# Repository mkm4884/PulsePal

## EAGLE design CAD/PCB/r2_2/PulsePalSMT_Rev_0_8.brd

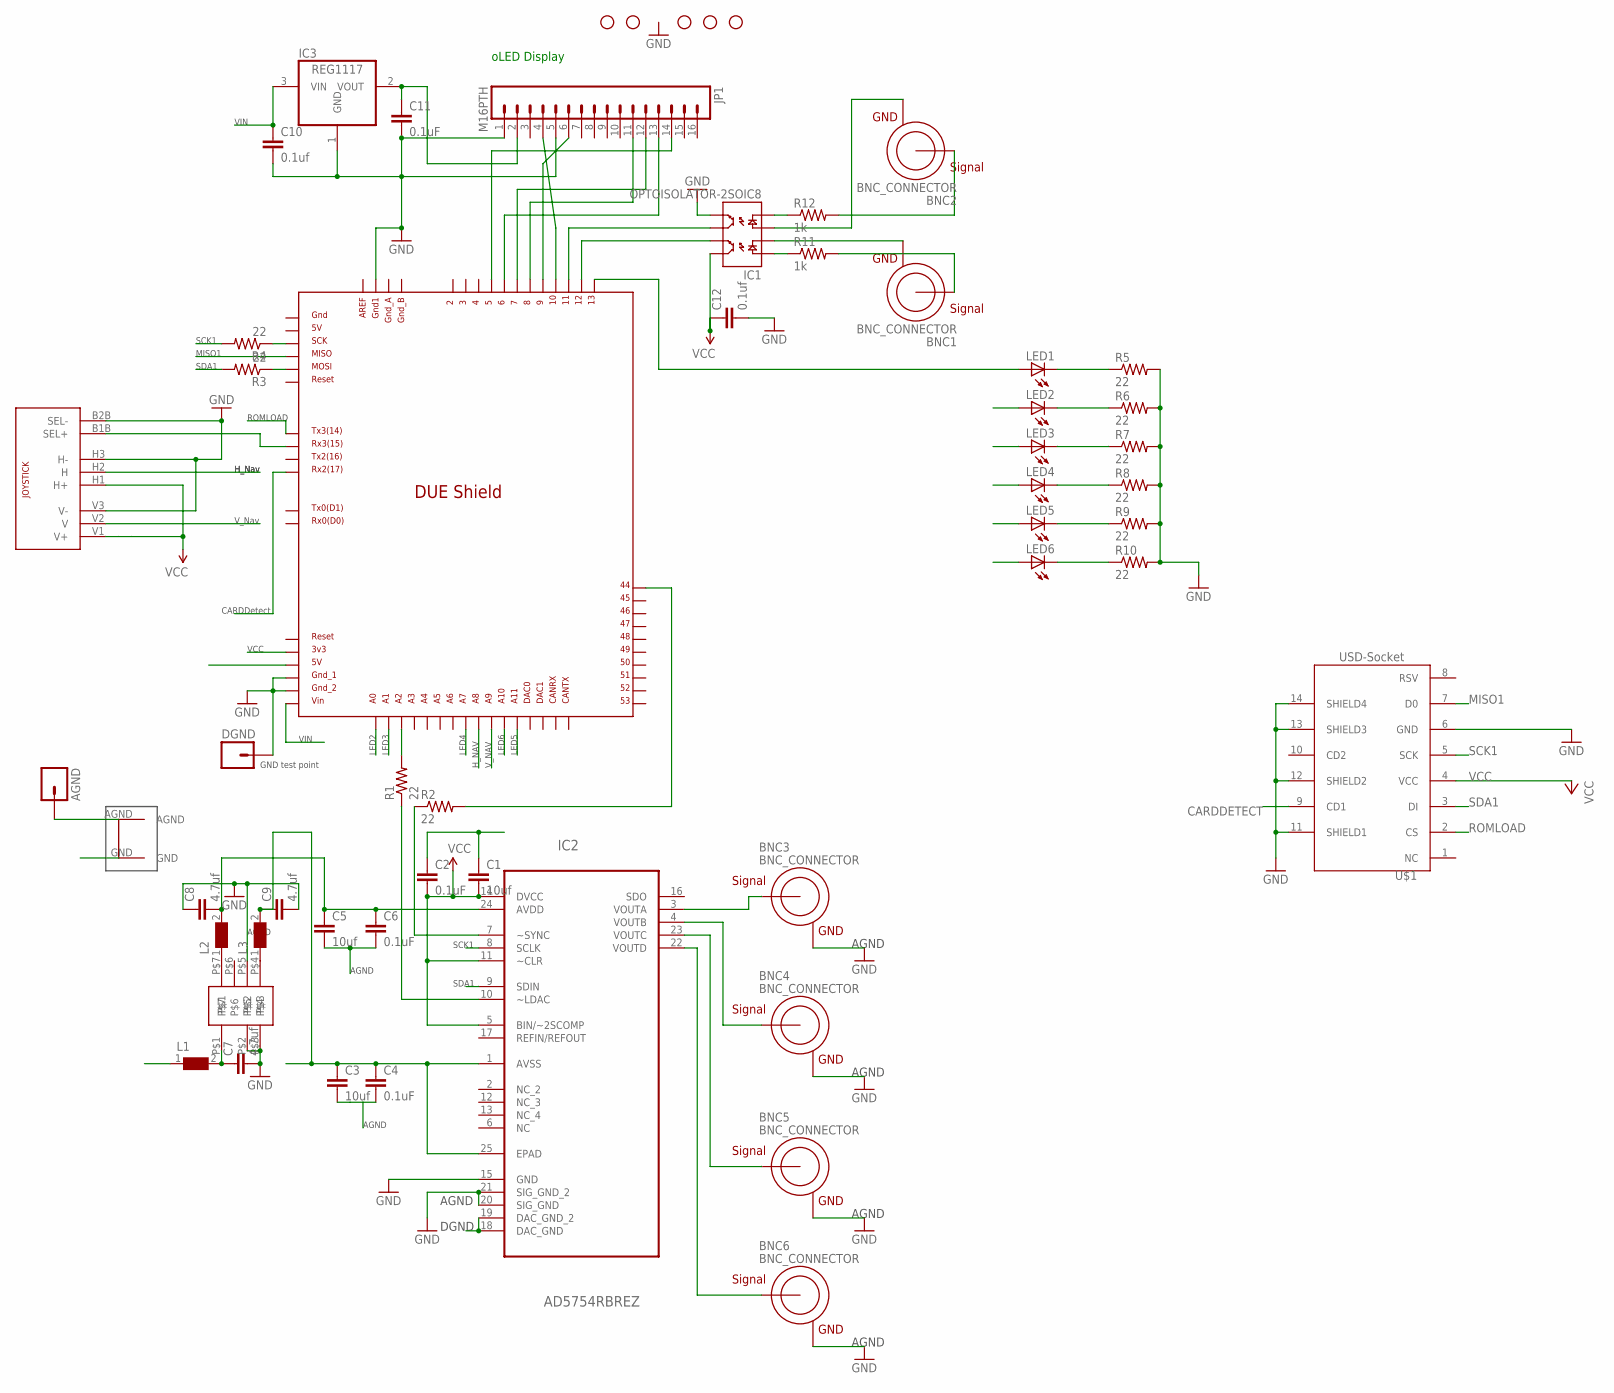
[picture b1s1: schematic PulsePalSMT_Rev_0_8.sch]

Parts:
AGND: M01PTH; 1X01
ARDUINO: DUE(NORMAL)
BNC1, BNC2, BNC3, BNC4, BNC5, BNC6: BNC_CONNECTOR
C1, C3, C5: 10uf; 1206@1
C2, C4, C6, C11: 0.1uF; 0805
C7, C8, C9: 4.7uf; 1206@1
C10: 0.1uf; 0805
C12: 0.1uf; 1206@1
DGND: M01PTH; 1X01
IC1: OPTOISOLATOR-2SOIC8; SO08-2
IC2: AD5754RBREZ; SOP65P640X120-25N
IC3: REG1117; SOT223
JP1: M16PTH; 1X16
JP2, JP5, JP6, JP8, JP9: STAND-OFF
JS1: RKJXV1124
L1, L2, L3: WE-CBF-742792118_1206; 1206
LED1, LED2, LED3, LED4, LED5, LED6: LEDCHIPLED_1206; CHIPLED_1206
R1, R2, R3, R4, R5, R6, R7, R8, R9, R10: 22; 1206
R11, R12: 1k; 1206
U2: TDK_LAMBDA_5_TO_BI_12_125MA
U3: 502570-0893
U$6: GNDPLANESHRT

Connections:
5V: ARDUINO.5V, C1.2, C2.2, IC2.5 (BIN/~2SCOMP), IC2.11 (~CLR), IC2.14 (DVCC), L1.1
AGND: AGND.1, BNC3.GND, BNC4.GND, BNC5.GND, BNC6.GND, C3.2, C4.2, C5.2, C6.2, IC2.15 (GND), IC2.18 (DAC_GND), IC2.19 (DAC_GND_2), IC2.20 (SIG_GND), IC2.21 (SIG_GND_2), U$6.AGND
CARDDETECT: ARDUINO.RX2, U3.9 (CD1)
GND: ARDUINO.GND1, ARDUINO.GND_1, ARDUINO.GND_2, C1.1, C2.1, C7.2, C8.1, C9.2, C10.2, C11.2, C12.2, DGND.1, IC1.5 (EM2), IC3.1 (GND), JP1.1, JP1.5, JS1.B2B (SEL-), JS1.H3 (H-), JS1.V3 (V-), R5.2, R6.2, R7.2, R8.2, R9.2, R10.2, U2.P$2, U2.P$3, U2.P$5, U3.6 (GND), U3.11 (SHIELD1), U3.12 (SHIELD2), U3.13 (SHIELD3), U3.14 (SHIELD4), U$6.GND
H_NAV: ARDUINO.A8, JS1.H2 (H)
LED2: ARDUINO.A0, LED2.A
LED3: ARDUINO.A1, LED3.A
LED4: ARDUINO.A7, LED4.A
LED5: ARDUINO.A11, LED5.A
LED6: ARDUINO.A10, LED6.A
MISO1: ARDUINO.MISO_ICSP, U3.7 (D0)
unnamed: L2.1, U2.P$7
unnamed: L3.1, U2.P$4
unnamed: BNC3.SIGNAL, IC2.3 (VOUTA)
unnamed: BNC4.SIGNAL, IC2.4 (VOUTB)
unnamed: BNC5.SIGNAL, IC2.23 (VOUTC)
unnamed: BNC6.SIGNAL, IC2.22 (VOUTD)
unnamed: BNC1.GND, IC1.2 (C1)
unnamed: BNC1.SIGNAL, R11.2
unnamed: BNC2.GND, IC1.3 (A2)
unnamed: BNC2.SIGNAL, R12.2
unnamed: ARDUINO.SCK_ICSP, R4.1
unnamed: ARDUINO.MOSI_ICSP, R3.1
unnamed: ARDUINO.44, R2.2
unnamed: ARDUINO.A2, R1.2
unnamed: IC2.7 (~SYNC), R2.1
unnamed: IC2.10 (~LDAC), R1.1
unnamed: ARDUINO.RX3, JS1.B1B (SEL+)
unnamed: ARDUINO.11, IC1.6 (CL2)
unnamed: C11.1, IC3.2 (VOUT), JP1.2
unnamed: LED1.C, R5.1
unnamed: LED2.C, R6.1
unnamed: LED3.C, R7.1
unnamed: LED4.C, R8.1
unnamed: LED5.C, R9.1
unnamed: LED6.C, R10.1
unnamed: IC1.1 (A1), R11.1
unnamed: IC1.4 (C2), R12.1
unnamed: ARDUINO.12, IC1.7 (EM1)
unnamed: ARDUINO.5, JP1.14
unnamed: ARDUINO.13, LED1.A
unnamed: ARDUINO.10, JP1.4
unnamed: ARDUINO.9, JP1.6
unnamed: ARDUINO.8, JP1.11
unnamed: ARDUINO.7, JP1.12
unnamed: ARDUINO.6, JP1.13
unnamed: C5.1, C6.1, C8.2, IC2.24 (AVDD), L2.2
unnamed: C3.1, C4.1, C9.1, IC2.1 (AVSS), IC2.25 (EPAD), L3.2
unnamed: C7.1, L1.2, U2.P$1
ROMLOAD: ARDUINO.TX3, U3.2 (CS)
SCK1: IC2.8 (SCLK), R4.2, U3.5 (SCK)
SDA1: IC2.9 (SDIN), R3.2, U3.3 (DI)
VCC: ARDUINO.3V3, C12.1, IC1.8 (CL1), JS1.H1 (H+), JS1.V1 (V+), U3.4 (VCC)
VIN: ARDUINO.VIN, C10.1, IC3.3 (VIN)
V_NAV: ARDUINO.A9, JS1.V2 (V)

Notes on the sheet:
oLED Display
AGND
SCK1
SDA1
DGND
VCC
ROMLOAD
LED2
LED3
LED4
LED5
LED6
GND test point
H_Nav
V_Nav
MISO1
H_NAV
V_NAV
VIN
CARDDetect

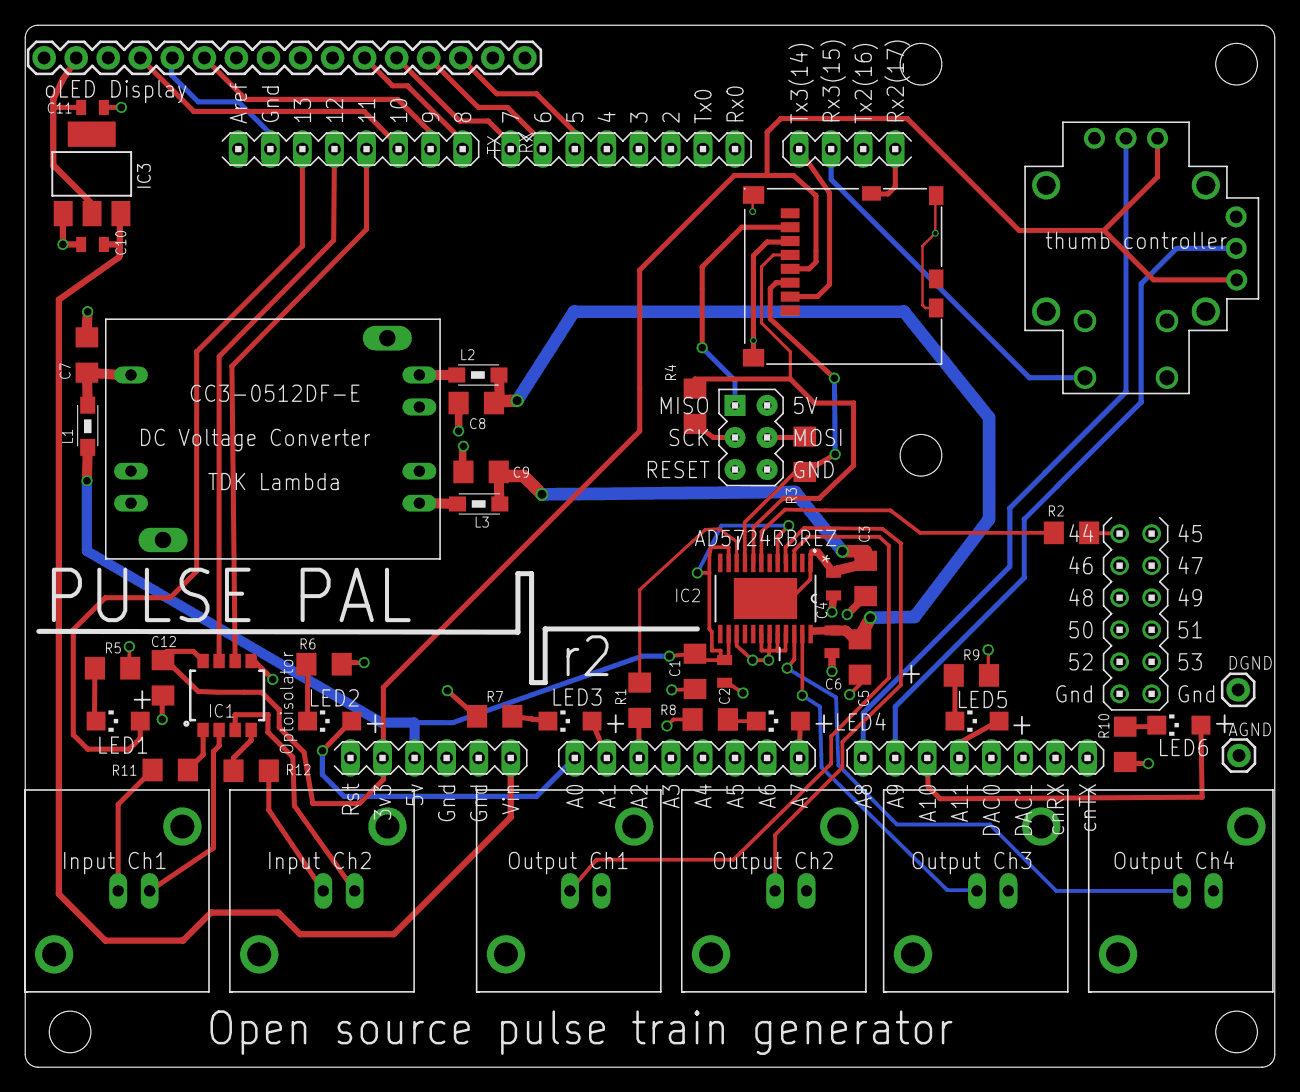
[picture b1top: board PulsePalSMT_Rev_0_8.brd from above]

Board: 4 copper layers, 99.0 x 82.6 mm, 55 parts (0 on the bottom side), 55 nets.

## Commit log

2019-08-09 Added r2.2 of the PCB to fit new SD card and thumbstick dimensions

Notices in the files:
parts and their libraries:
SparkFun-Resistors: Licensing: Creative Commons ShareAlike 4.0 International - https://creativecommons.org/licenses/by-sa/4.0
